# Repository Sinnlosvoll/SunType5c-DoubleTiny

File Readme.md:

# What is this about? #
This project aims to connect a Sun Type 5c I found to a pc without any drivers and only with the help of 2 Attiny85s.

## Why don't I keep this to myself but publish it to github? ##
Because I am a generous person and don't want to keep this to myself. Also if someone finds one of those awesome keyboards, they should be able to use it.
And I want a central storage for all my stuff/documentation and file versioning. Mostly the last one. ^^

## Why 2 ICs and not 1? ##
Initially I planned to do all the polling and USB reporting on a single AT85; but that wouldn't work. 
The realtime components of emulating a USB device via software [(V-USB)](http://www.obdev.at/products/vusb/index-de.html) and the relatively low baud on the keyboard side of 1200 conflicted.
So two should resolve that hurdle by decoupling those two requirements while still allowing me to complete this project without expensive and larger flasher and boards.

## So what's the plan, chief? ##
Basically there is a master AT85, which handles USB communication and a buffer AT85 which handles communication with the keyboard and acts as a two-way buffer for events and commands.

# Now it's gonna get technical, be warned. #

### USB ###
The hardware-USB-implementation is heavily *cough* borrowed *cough* from [codeandlifes.com blog entry](http://codeandlife.com/2012/02/22/v-usb-with-attiny45-attiny85-without-a-crystal/).
The plan looks like this: 
Software is (as of right now) based on [another blog entry](http://codeandlife.com/2012/06/18/usb-hid-keyboard-with-v-usb/) and extended by myself.

### Keyboard interface ###
The Type 5c uses an async 1200 baud non-inverted signal with one bit to signal the start of a transfer and then following 8 bit. If the last bit is high, then this is the last bit in this message. Else the reciever should wait for more packets.

That is my personal experience using a logic analyzer, so official documentation might differ, but that is really hard to prove with the lack of official documentation out there. I found a document describing general Sparc keyboard, altough I lost the sourcelink. You can find it it [documentation/Sparcs.pdf](documentation/Sparcs.pdf)

### Tiny-Tiny-interface ###
The two IC's are connected via 2 wired, both with a 4.7K pull-down to ground. The slave signals communication by rasing its flow-control-line high, so the master doesn't request any data. If the flwcntrl is low, then the master can send a 8-bit command to the slave, by raising it's txd for 70µ, then sending each bit for 70µs afterwards. The slave never initiates transfers.
If the command requires a respone such as ("what keys where pressed?") the master raises the flwcntrl line for each bit and the slave shall send one bit as long as the flwcntrl line is kept high. The master then pulles it low for 10µs and requests the next bit. *This is slow but probably needed to keep the master idling enough for v-usb to work*.

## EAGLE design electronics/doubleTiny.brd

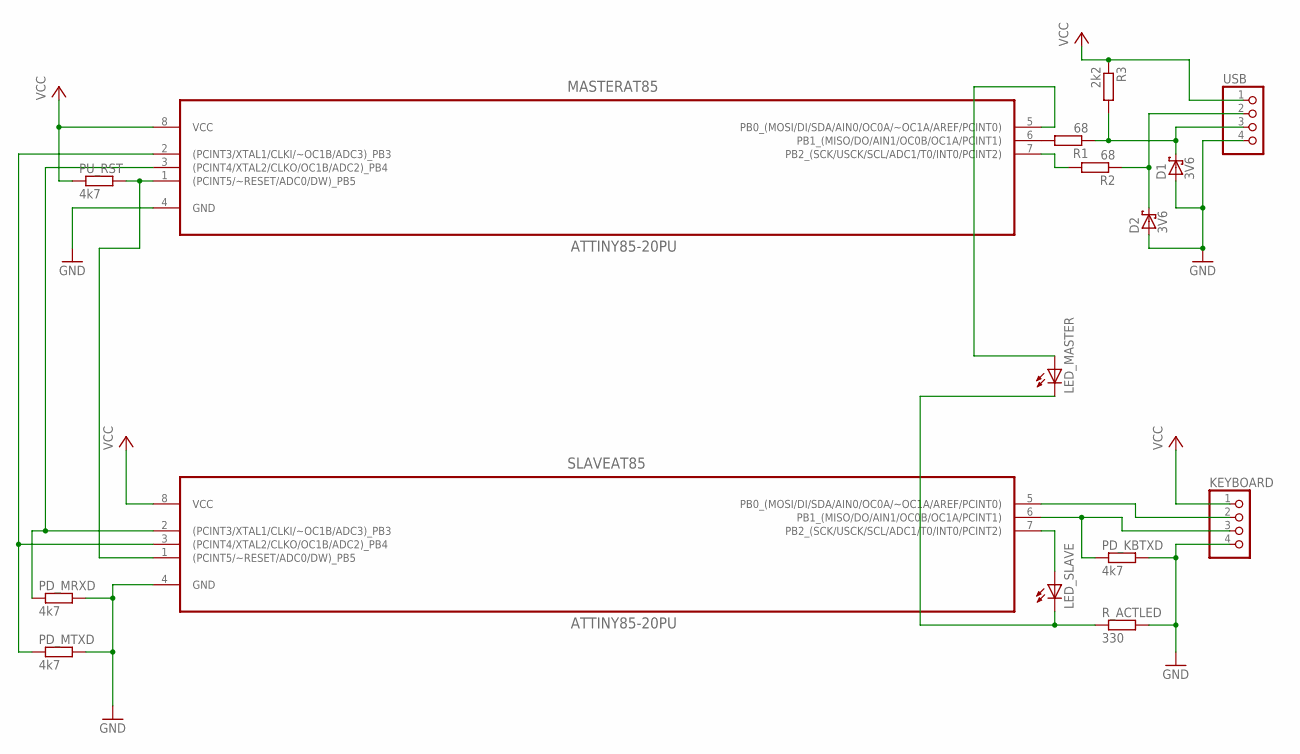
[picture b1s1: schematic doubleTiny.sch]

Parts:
D1, D2: 3V6; C4111-15
KEYBOARD: PINHD-1X4; 1X04
LED_MASTER: LED3MM
LED_SLAVE: LED5MM
MASTERAT85: ATTINY85-20PU; DIP254P762X533-8
PD_KBTXD: 4k7; 0309/12
PD_MRXD: 4k7; 0309/12
PD_MTXD: 4k7; 0309/12
PU_RST: 4k7; 0309/12
R1, R2: 68; 0309/12
R3: 2k2; 0309/12
R_ACTLED: 330; 0309/12
SLAVEAT85: ATTINY85-20PU; DIP254P762X533-8
USB: PINHD-1X4; 1X04

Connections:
GND: D1.A, D2.A, KEYBOARD.4, MASTERAT85.4 (GND), PD_KBTXD.2, PD_MRXD.2, PD_MTXD.2, R_ACTLED.2, SLAVEAT85.4 (GND), USB.4
unnamed: MASTERAT85.7 (PB2_(SCK/USCK/SCL/ADC1/T0/INT0/PCINT2)), R2.2
unnamed: MASTERAT85.6 (PB1_(MISO/DO/AIN1/OC0B/OC1A/PCINT1)), R1.2
unnamed: D1.C, R1.1, R3.2, USB.3
unnamed: D2.C, R2.1, USB.2
unnamed: KEYBOARD.2, SLAVEAT85.5 (PB0_(MOSI/DI/SDA/AIN0/OC0A/~OC1A/AREF/P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)
unnamed: MASTERAT85.3 ((PCINT4/XTAL2/CLKO/OC1B/ADC2)_PB4), PD_MRXD.1, SLAVEAT85.2 ((PCINT3/XTAL1/CLKI/~OC1B/ADC3)_PB3)
unnamed: MASTERAT85.2 ((PCINT3/XTAL1/CLKI/~OC1B/ADC3)_PB3), PD_MTXD.1, SLAVEAT85.3 ((PCINT4/XTAL2/CLKO/OC1B/ADC2)_PB4)
unnamed: KEYBOARD.3, PD_KBTXD.1, SLAVEAT85.6 (PB1_(MISO/DO/AIN1/OC0B/OC1A/PCINT1))
unnamed: MASTERAT85.1 ((PCINT5/~RESET/ADC0/DW)_PB5), PU_RST.2, SLAVEAT85.1 ((PCINT5/~RESET/ADC0/DW)_PB5)
unnamed: LED_MASTER.A, MASTERAT85.5 (PB0_(MOSI/DI/SDA/AIN0/OC0A/~OC1A/AREF/P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)
unnamed: LED_SLAVE.A, SLAVEAT85.7 (PB2_(SCK/USCK/SCL/ADC1/T0/INT0/PCINT2))
unnamed: LED_MASTER.K (C), LED_SLAVE.K (C), R_ACTLED.1
VCC: KEYBOARD.1, MASTERAT85.8 (VCC), PU_RST.1, R3.1, SLAVEAT85.8 (VCC), USB.1

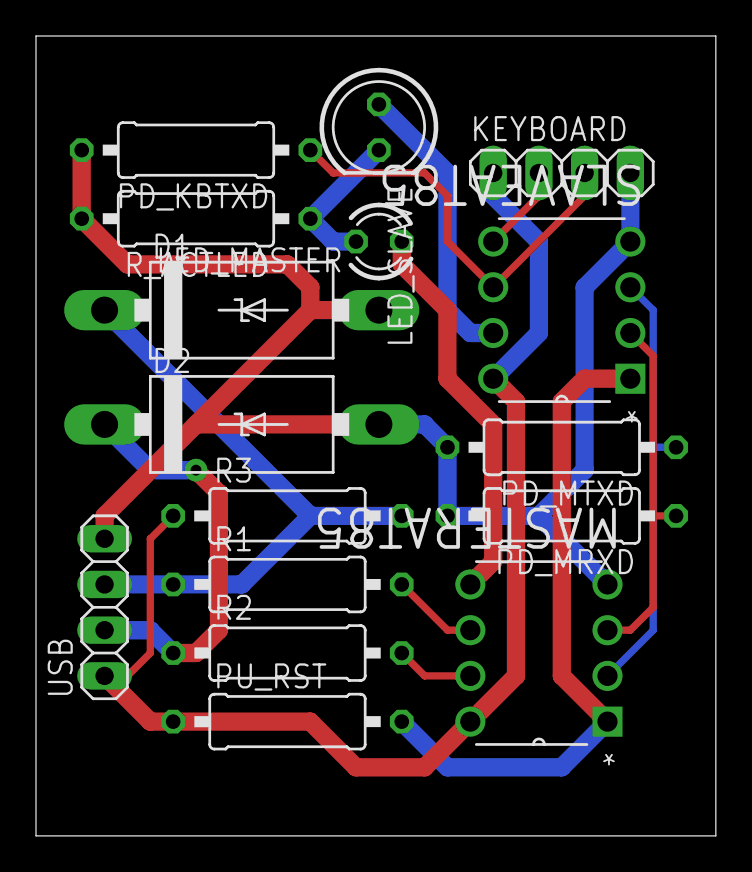
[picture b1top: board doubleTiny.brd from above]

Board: 2 copper layers, 37.8 x 44.4 mm, 16 parts (0 on the bottom side), 14 nets.

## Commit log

2015-03-28 :circus_tent: Added .gitattributes
2015-03-29 created readme and added files
    Created initial markdown explaining my goals and added pcb, schematics
    and some documentation from sparc i found somewhere
2015-03-29 show image in readme
    hopefully
2015-03-29 fixing lettercase in readme
2015-03-29 added pcb image
2015-03-29 added wrong image before
2015-03-29 added files from first try
    The license, in this case GPL3, only applies to files in /software, not
    documentation. The pdfs still belong to their rightful owners or
    rightholders. Not me
2015-03-29 added gitignore file
2015-04-16 renamed master to usb and created kbdTiny folder
2015-04-27 updatet schematics and used usbT for capsLock
2015-04-28 created first board layout and added led to master. Swapped usb pins and conglomerated resets
2015-06-10 cahnged pins in software for keyboard side and stubbed interupts
2015-06-11 added basic internal communication support to keyboardtiny. Note yet tested
2015-06-11 fixed readingdisplay in main loop kb-tiny and cleanup
2015-06-14 moved USBSendbuffer to be immediately send upon request
2015-06-15 pin fixes in kbT; pin-states and recieve function in usbT
2015-06-15 removed old junk and interupts from usbT and implemented read/write to kbT. untested as always
2015-06-16 cleanup of usbT and interrupts only when something changed
2015-06-16 minor fixes to allow compiling
2015-06-16 changed kbT response to rise from falling and rise, disabled useless timers and documented some parts
2015-06-17 fixed writing zeroes, changed timing for kbT-usbT communication
2015-06-18 changed kbT interrupt behaviour but it's not working yet. Adjusted timings and added asynchronous sending of messages from usbT to kbT
